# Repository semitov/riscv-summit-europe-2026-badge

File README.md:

# RISC-V Summit Europe 2026 Badge

Electronic badge PCB for RISC-V Summit Europe 2026 in Bologna, Italy. Designed in KiCad 10.

## Gallery

- Render of the badge on KiCad

## License and Credits
Designed by: [Tan Siret Akıncı](https://github.com/tansiret), [Emanuele De Paoli](https://github.com/Irdyad), [Carlo Bendelli](https://github.com/CALIOSTRO7), [Valerio Donnini](https://github.com/Valerio-Donnini) and [Alessandro Bocchino](https://github.com/AleB-04).
This open source hardware project is licensed with [CERN-OHL-W](LICENSE). The project is sponsored by © 2026 [RISC-V International](), [NextPCB](https://www.nextpcb.com/), [GOWIN Semiconductor](https://www.gowinsemi.com/en/) and  [DeepComputing](https://deepcomputing.io/).
The project has been certified by [OSHWA](https://oshwa.org/) as Open Source Hardware (UID: [IT000028](https://certification.oshwa.org/it000028.html)).
</br>

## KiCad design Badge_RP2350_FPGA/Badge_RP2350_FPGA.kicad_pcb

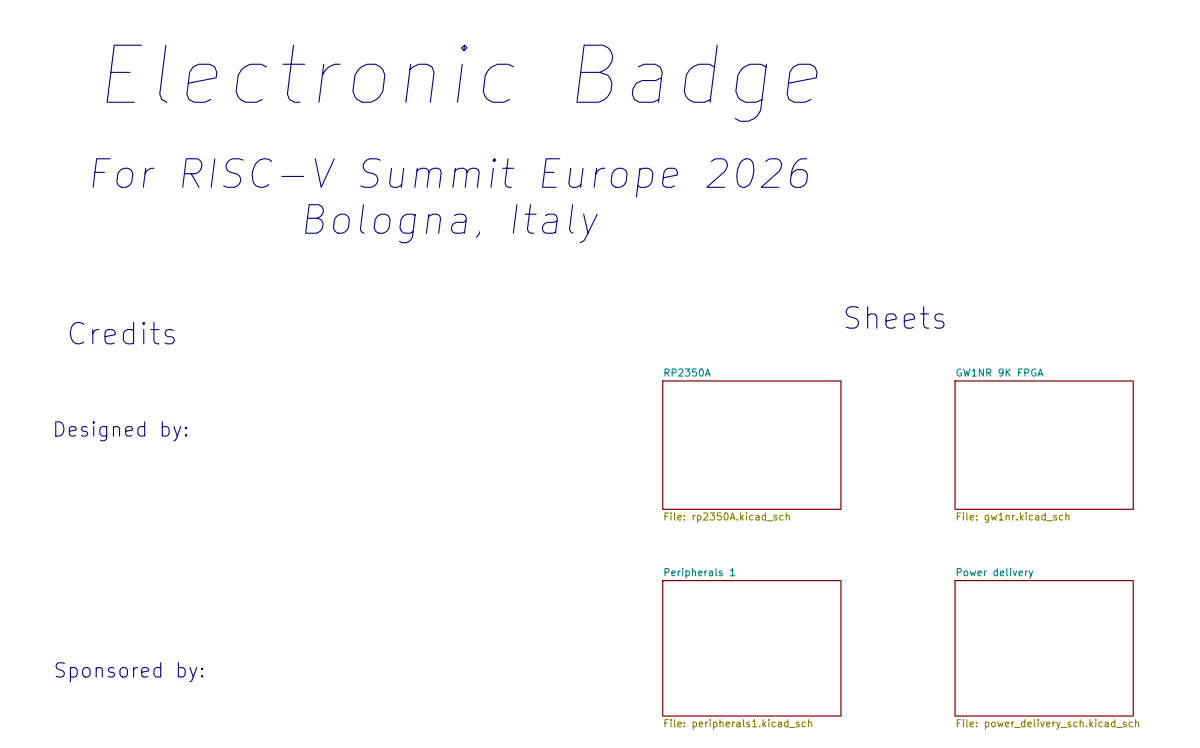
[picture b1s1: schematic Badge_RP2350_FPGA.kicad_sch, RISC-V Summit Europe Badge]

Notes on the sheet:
Sheets
Credits
Electronic Badge
Sponsored by:
For RISC-V Summit Europe 2026 Bologna, Italy
Designed by:

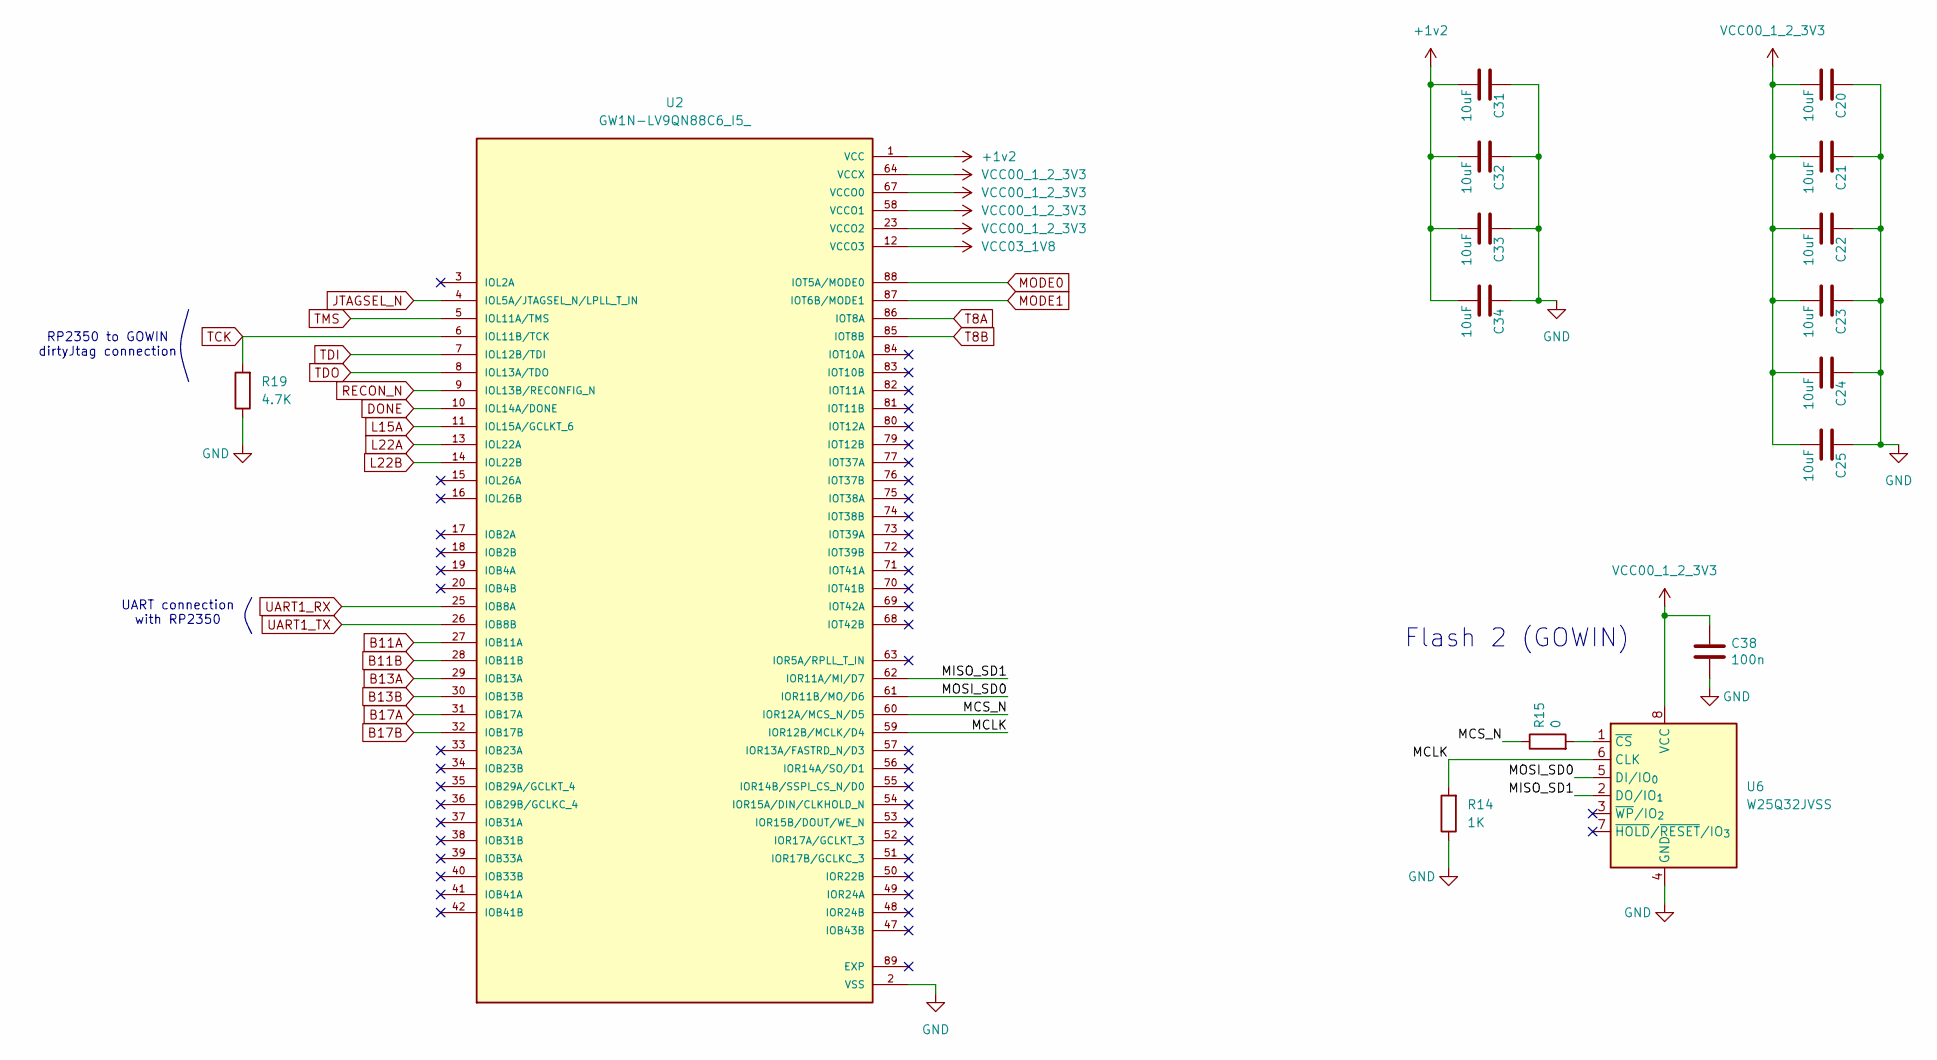
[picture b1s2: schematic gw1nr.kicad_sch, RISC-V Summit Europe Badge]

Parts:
C20, C21, C22, C23, C24, C25, C31, C32, C33, C34: 10uF; C_0402_1005Metric
C38: 100n; C_0402_1005Metric
R14: 1K; R_0402_1005Metric
R15: 0; R_0402_1005Metric
R19: 4.7K; R_0402_1005Metric
U2: GW1N-LV9QN88C6_I5_; QFN40P1000X1000X95-89N; PARTREV UG103-2.3E
U6: W25Q32JVSS; SOIC-8_5.3x5.3mm_P1.27mm

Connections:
/GW1NR 9K FPGA/MCLK: R14.2, U2.59 (IOR12B/MCLK/D4), U6.6 (CLK)
/GW1NR 9K FPGA/MCS_N: R15.1, U2.60 (IOR12A/MCS_N/D5)
/GW1NR 9K FPGA/MISO_SD1: U2.62 (IOR11A/MI/D7), U6.2 (DO/IO_{1})
/GW1NR 9K FPGA/MOSI_SD0: U2.61 (IOR11B/MO/D6), U6.5 (DI/IO_{0})
B11A: U2.27 (IOB11A); also elsewhere on the board
B11B: U2.28 (IOB11B); also elsewhere on the board
B13A: U2.29 (IOB13A); also elsewhere on the board
B13B: U2.30 (IOB13B); also elsewhere on the board
B17A: U2.31 (IOB17A); also elsewhere on the board
B17B: U2.32 (IOB17B); also elsewhere on the board
DONE: U2.10 (IOL14A/DONE); also elsewhere on the board
GND: C20.1, C21.1, C22.1, C23.1, C24.1, C25.1, C31.1, C32.1, C33.1, C34.1, C38.2, R14.1, R19.1, U2.2 (VSS), U2.21 (VSS), U2.24 (VSS), U2.43 (VSS), U2.46 (VSS), U2.65 (VSS), U6.4 (GND); also elsewhere on the board
JTAGSEL_N: U2.4 (IOL5A/JTAGSEL_N/LPLL_T_IN); also elsewhere on the board
L15A: U2.11 (IOL15A/GCLKT_6); also elsewhere on the board
L22A: U2.13 (IOL22A); also elsewhere on the board
L22B: U2.14 (IOL22B); also elsewhere on the board
MODE0: U2.88 (IOT5A/MODE0); also elsewhere on the board
MODE1: U2.87 (IOT6B/MODE1); also elsewhere on the board
unnamed: R15.2, U6.1 (~CS)
RECON_N: U2.9 (IOL13B/RECONFIG_N); also elsewhere on the board
T8A: U2.86 (IOT8A); also elsewhere on the board
T8B: U2.85 (IOT8B); also elsewhere on the board
TCK: R19.2, U2.6 (IOL11B/TCK); also elsewhere on the board
TDI: U2.7 (IOL12B/TDI); also elsewhere on the board
TDO: U2.8 (IOL13A/TDO); also elsewhere on the board
TMS: U2.5 (IOL11A/TMS); also elsewhere on the board
UART1_RX: U2.25 (IOB8A); also elsewhere on the board
UART1_TX: U2.26 (IOB8B); also elsewhere on the board
VCC00_1_2_3V3: C20.2, C21.2, C22.2, C23.2, C24.2, C25.2, C38.1, U2.23 (VCCO2), U2.44 (VCCO2), U2.58 (VCCO1), U2.64 (VCCX), U2.67 (VCCO0), U2.78 (VCCX), U6.8 (VCC); also elsewhere on the board
VCC03_1V8: U2.12 (VCCO3); also elsewhere on the board

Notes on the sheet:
RP2350 to GOWIN dirtyJtag connection
UART connection with RP2350
Flash 2 (GOWIN)

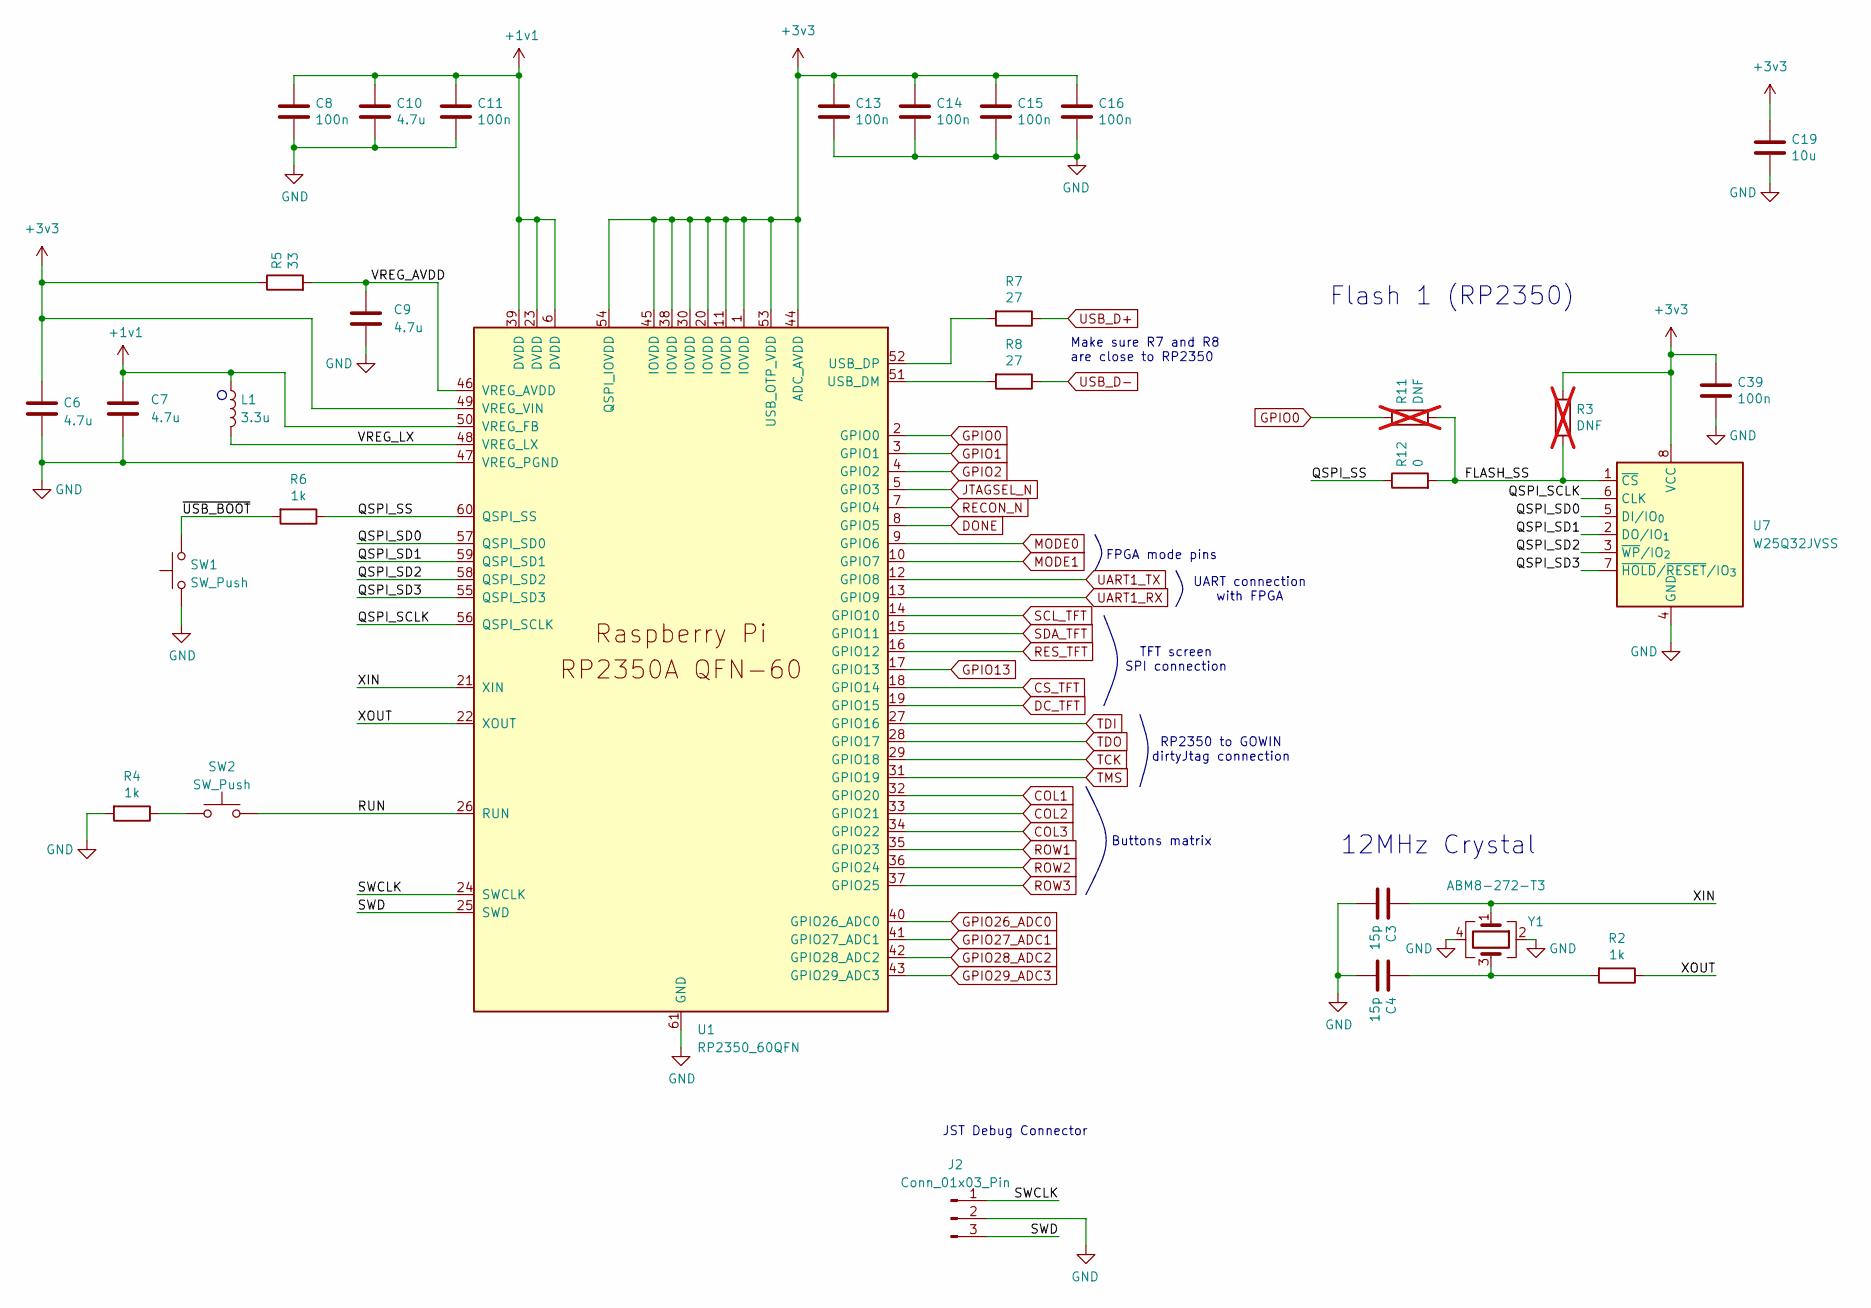
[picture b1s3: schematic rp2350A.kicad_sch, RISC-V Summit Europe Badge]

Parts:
C3, C4: 15p; C_0402_1005Metric
C6, C7, C9, C10: 4.7u; C_0402_1005Metric
C8, C11, C13, C14, C15, C16, C39: 100n; C_0402_1005Metric
C19: 10u; C_0805_2012Metric
J2: Conn_01x03_Pin; PinHeader_1x03_P2.54mm_Vertical
L1: 3.3u; L_pol_2016
R2, R4, R6: 1k; R_0402_1005Metric
R3, R11: DNF; R_0402_1005Metric; not fitted
R5: 33; R_0402_1005Metric
R7, R8: 27; R_0402_1005Metric
R12: 0; R_0402_1005Metric
SW1, SW2: SW_Push; C&K KMR621NGLFS
U1: RP2350_60QFN; RP2350-QFN-60-1EP_7x7_P0.4mm_EP3.4x3.4mm_ThermalVias
U7: W25Q32JVSS; SOIC-8_5.3x5.3mm_P1.27mm
Y1: ABM8-272-T3; Crystal_SMD_3225-4Pin_3.2x2.5mm

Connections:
+1v1: C7.1, C8.1, C10.1, C11.1, L1.1, U1.6 (DVDD), U1.23 (DVDD), U1.39 (DVDD), U1.50 (VREG_FB)
+3v3: C6.1, C13.1, C14.1, C15.1, C16.1, C19.1, C39.1, R3.1, R5.1, U1.1 (IOVDD), U1.11 (IOVDD), U1.20 (IOVDD), U1.30 (IOVDD), U1.38 (IOVDD), U1.44 (ADC_AVDD), U1.45 (IOVDD), U1.49 (VREG_VIN), U1.53 (USB_OTP_VDD), U1.54 (QSPI_IOVDD), U7.8 (VCC); also elsewhere on the board
/RP2350A/FLASH_SS: R3.2, R11.2, R12.2, U7.1 (~CS)
/RP2350A/QSPI_SCLK: U1.56 (QSPI_SCLK), U7.6 (CLK)
/RP2350A/QSPI_SD0: U1.57 (QSPI_SD0), U7.5 (DI/IO_{0})
/RP2350A/QSPI_SD1: U1.59 (QSPI_SD1), U7.2 (DO/IO_{1})
/RP2350A/QSPI_SD2: U1.58 (QSPI_SD2), U7.3 (~WP/IO_{2})
/RP2350A/QSPI_SD3: U1.55 (QSPI_SD3), U7.7 (~HOLD/~RESET/IO_{3})
/RP2350A/QSPI_SS: R6.1, R12.1, U1.60 (QSPI_SS)
/RP2350A/RUN: SW2.2, U1.26 (RUN)
/RP2350A/SWCLK: J2.1, U1.24 (SWCLK)
/RP2350A/SWD: J2.3, U1.25 (SWD)
/RP2350A/VREG_AVDD: C9.1, R5.2, U1.46 (VREG_AVDD)
/RP2350A/VREG_LX: L1.2, U1.48 (VREG_LX)
/RP2350A/XIN: C3.1, U1.21 (XIN), Y1.1
/RP2350A/XOUT: R2.1, U1.22 (XOUT)
/RP2350A/~USB_BOOT: R6.2, SW1.2
COL1: U1.32 (GPIO20); also elsewhere on the board
COL2: U1.33 (GPIO21); also elsewhere on the board
COL3: U1.34 (GPIO22); also elsewhere on the board
CS_TFT: U1.18 (GPIO14); also elsewhere on the board
DC_TFT: U1.19 (GPIO15); also elsewhere on the board
DONE: U1.8 (GPIO5); also elsewhere on the board
GND: C3.2, C4.2, C6.2, C7.2, C8.2, C9.2, C10.2, C11.2, C13.2, C14.2, C15.2, C16.2, C19.2, C39.2, J2.2, R4.2, SW1.1, U1.47 (VREG_PGND), U1.61 (GND), U7.4 (GND), Y1.2, Y1.4; also elsewhere on the board
GPIO0: R11.1, U1.2 (GPIO0); also elsewhere on the board
GPIO1: U1.3 (GPIO1)
GPIO2: U1.4 (GPIO2)
GPIO13: U1.17 (GPIO13)
GPIO26_ADC0: U1.40 (GPIO26_ADC0); also elsewhere on the board
GPIO27_ADC1: U1.41 (GPIO27_ADC1); also elsewhere on the board
GPIO28_ADC2: U1.42 (GPIO28_ADC2); also elsewhere on the board
GPIO29_ADC3: U1.43 (GPIO29_ADC3); also elsewhere on the board
JTAGSEL_N: U1.5 (GPIO3); also elsewhere on the board
MODE0: U1.9 (GPIO6); also elsewhere on the board
MODE1: U1.10 (GPIO7); also elsewhere on the board
unnamed: C4.1, R2.2, Y1.3
unnamed: R4.1, SW2.1
unnamed: R8.2, U1.51 (USB_DM)
unnamed: R7.2, U1.52 (USB_DP)
RECON_N: U1.7 (GPIO4); also elsewhere on the board
RES_TFT: U1.16 (GPIO12); also elsewhere on the board
ROW1: U1.35 (GPIO23); also elsewhere on the board
ROW2: U1.36 (GPIO24); also elsewhere on the board
ROW3: U1.37 (GPIO25); also elsewhere on the board
SCL_TFT: U1.14 (GPIO10); also elsewhere on the board
SDA_TFT: U1.15 (GPIO11); also elsewhere on the board
TCK: U1.29 (GPIO18); also elsewhere on the board
TDI: U1.27 (GPIO16); also elsewhere on the board
TDO: U1.28 (GPIO17); also elsewhere on the board
TMS: U1.31 (GPIO19); also elsewhere on the board
UART1_RX: U1.13 (GPIO9); also elsewhere on the board
UART1_TX: U1.12 (GPIO8); also elsewhere on the board
USB_D+: R7.1; also elsewhere on the board
USB_D-: R8.1; also elsewhere on the board

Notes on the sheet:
Flash 1 (RP2350)
JST Debug Connector
Make sure R7 and R8 are close to RP2350
TFT screen SPI connection
FPGA mode pins
UART connection with FPGA
Buttons matrix
RP2350 to GOWIN dirtyJtag connection
12MHz Crystal

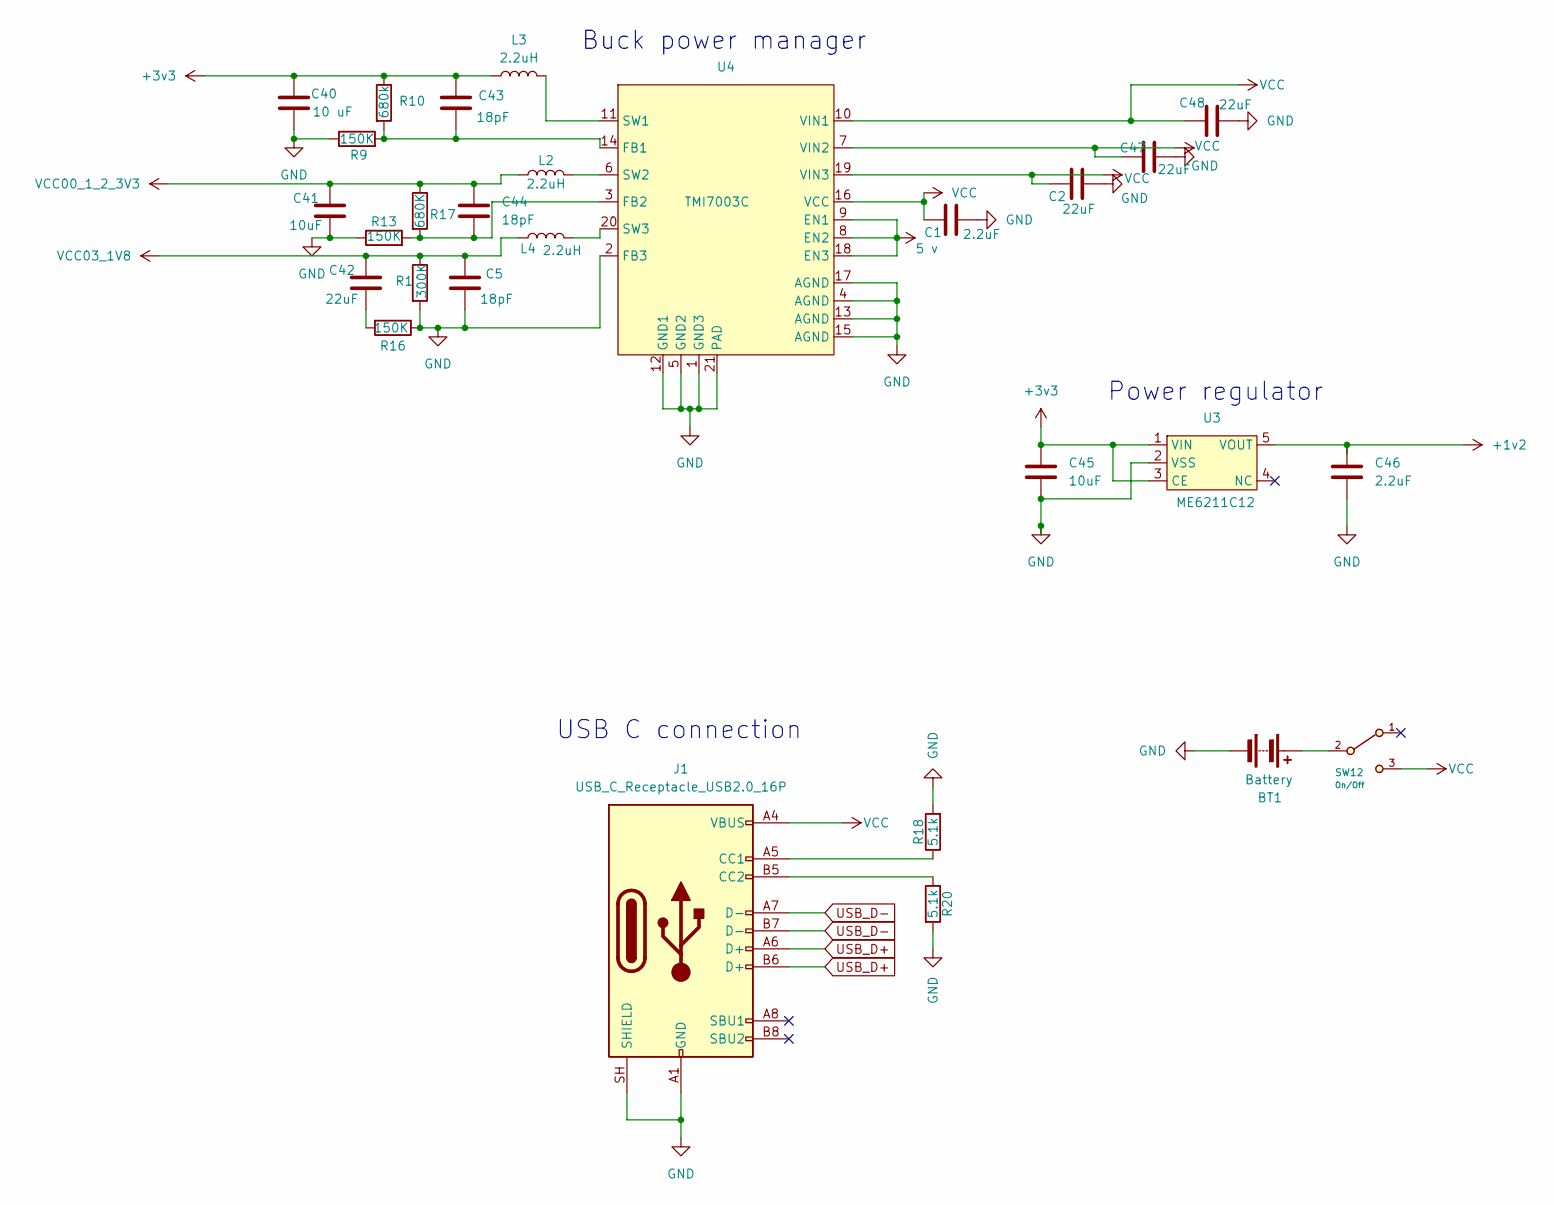
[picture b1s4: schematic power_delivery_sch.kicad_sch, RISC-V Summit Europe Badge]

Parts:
BT1: Battery; BatteryHolder_Keystone_2462_2xAA
C1, C46: 2.2uF; C_0402_1005Metric
C2, C42, C47, C48: 22uF; C_0402_1005Metric
C5, C43, C44: 18pF; C_0402_1005Metric
C40: 10 uF; C_0402_1005Metric
C41, C45: 10uF; C_0402_1005Metric
J1: USB_C_Receptacle_USB2.0_16P; USB_C_Receptacle_HRO_TYPE-C-31-M-12
L2, L3, L4: 2.2uH; L_APV_ANR4018
R1: 300K; R_0402_1005Metric
R9, R13, R16: 150K; R_0402_1005Metric
R10: 680k; R_0402_1005Metric
R17: 680K; R_0402_1005Metric
R18, R20: 5.1k; R_0402_1005Metric
SW12: On/Off; C&K JS102011SAQN
U3: ME6211C12; SOT-23-5_L3.0-W1.7-P0.95-LS2.8-BL
U4: TMI7003C; QFN-20_L3.0-W3.0-P0.40-BL-EP1.7

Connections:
5 v: U4.8 (EN2), U4.9 (EN1), U4.18 (EN3)
+3v3: C40.1, C43.1, C45.1, L3.1, R10.1, U3.1 (VIN), U3.3 (CE); also elsewhere on the board
GND: BT1.2 (-), C1.2, C2.2, C5.2, C40.2, C41.2, C45.2, C46.2, C47.2, C48.2, J1.A1 (GND), J1.A12 (GND), J1.B1 (GND), J1.B12 (GND), J1.SH (SHIELD), R1.2, R9.1, R13.1, R16.1, R18.2, R20.2, U3.2 (VSS), U4.1 (GND3), U4.2 (FB3), U4.4 (AGND), U4.5 (GND2), U4.12 (GND1), U4.13 (AGND), U4.15 (AGND), U4.17 (AGND), U4.21 (PAD); also elsewhere on the board
unnamed: BT1.1 (+), SW12.2 (B)
unnamed: C42.2, R16.2
unnamed: J1.A5 (CC1), R18.1
unnamed: J1.B5 (CC2), R20.1
unnamed: C43.2, R9.2, R10.2, U4.14 (FB1)
unnamed: C44.2, R13.2, R17.2, U4.3 (FB2)
unnamed: L3.2, U4.11 (SW1)
unnamed: L2.2, U4.6 (SW2)
unnamed: L4.2, U4.20 (SW3)
USB_D+: J1.A6 (D+), J1.B6 (D+); also elsewhere on the board
USB_D-: J1.A7 (D-), J1.B7 (D-); also elsewhere on the board
VCC00_1_2_3V3: C41.1, C44.1, L2.1, R17.1; also elsewhere on the board
VCC03_1V8: C5.1, C42.1, L4.1, R1.1; also elsewhere on the board

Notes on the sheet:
Power regulator
USB C connection
Buck power manager

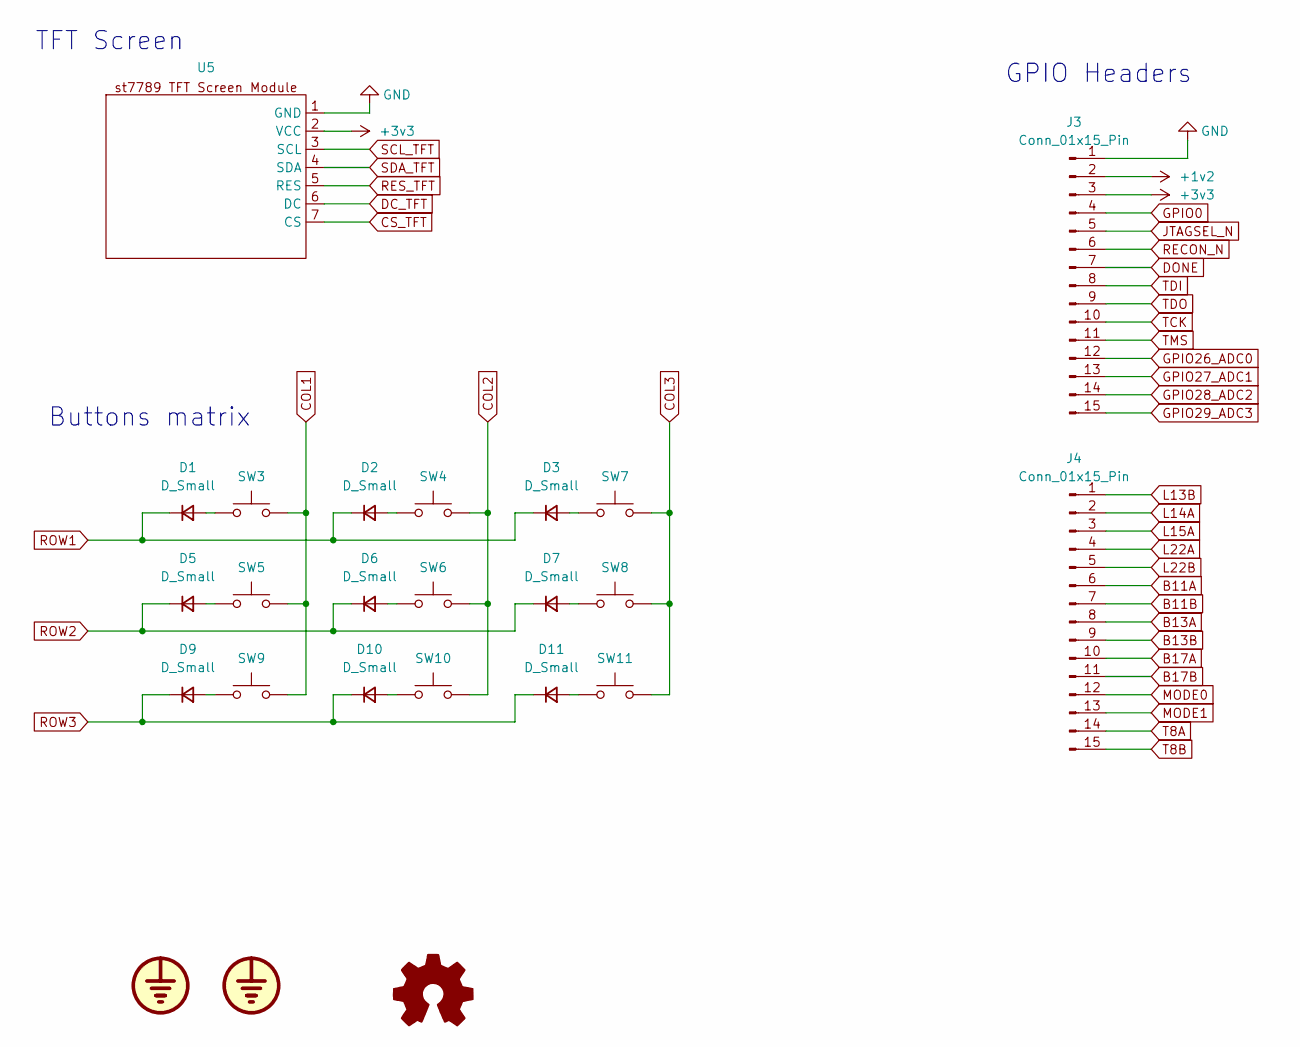
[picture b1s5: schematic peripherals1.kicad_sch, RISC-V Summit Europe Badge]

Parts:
D1, D2, D3, D5, D6, D7, D9, D10, D11: D_Small; Nexperia BAS516,115
J3, J4: Conn_01x15_Pin; PinHeader_1x15_P2.54mm_Vertical
SW3, SW4, SW5, SW6, SW7, SW8, SW9, SW10, SW11: SHOU HAN TS665PA 250gf
U5: st7789_7pin_noblk

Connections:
+3v3: J3.3, U5.2 (VCC); also elsewhere on the board
B11A: J4.6; also elsewhere on the board
B11B: J4.7; also elsewhere on the board
B13A: J4.8; also elsewhere on the board
B13B: J4.9; also elsewhere on the board
B17A: J4.10; also elsewhere on the board
B17B: J4.11; also elsewhere on the board
COL1: SW3.2, SW5.2, SW9.2; also elsewhere on the board
COL2: SW4.2, SW6.2, SW10.2; also elsewhere on the board
COL3: SW7.2, SW8.2, SW11.2; also elsewhere on the board
CS_TFT: U5.7 (CS); also elsewhere on the board
DC_TFT: U5.6 (DC); also elsewhere on the board
DONE: J3.7; also elsewhere on the board
GND: J3.1, U5.1 (GND); also elsewhere on the board
GPIO0: J3.4; also elsewhere on the board
GPIO26_ADC0: J3.12; also elsewhere on the board
GPIO27_ADC1: J3.13; also elsewhere on the board
GPIO28_ADC2: J3.14; also elsewhere on the board
GPIO29_ADC3: J3.15; also elsewhere on the board
JTAGSEL_N: J3.5; also elsewhere on the board
L13B: J4.1
L14A: J4.2
L15A: J4.3; also elsewhere on the board
L22A: J4.4; also elsewhere on the board
L22B: J4.5; also elsewhere on the board
MODE0: J4.12; also elsewhere on the board
MODE1: J4.13; also elsewhere on the board
unnamed: D1.2 (A), SW3.1
unnamed: D2.2 (A), SW4.1
unnamed: D3.2 (A), SW7.1
unnamed: D5.2 (A), SW5.1
unnamed: D6.2 (A), SW6.1
unnamed: D7.2 (A), SW8.1
unnamed: D9.2 (A), SW9.1
unnamed: D10.2 (A), SW10.1
unnamed: D11.2 (A), SW11.1
RECON_N: J3.6; also elsewhere on the board
RES_TFT: U5.5 (RES); also elsewhere on the board
ROW1: D1.1 (K), D2.1 (K), D3.1 (K); also elsewhere on the board
ROW2: D5.1 (K), D6.1 (K), D7.1 (K); also elsewhere on the board
ROW3: D9.1 (K), D10.1 (K), D11.1 (K); also elsewhere on the board
SCL_TFT: U5.3 (SCL); also elsewhere on the board
SDA_TFT: U5.4 (SDA); also elsewhere on the board
T8A: J4.14; also elsewhere on the board
T8B: J4.15; also elsewhere on the board
TCK: J3.10; also elsewhere on the board
TDI: J3.8; also elsewhere on the board
TDO: J3.9; also elsewhere on the board
TMS: J3.11; also elsewhere on the board

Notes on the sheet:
Buttons matrix
TFT Screen
GPIO Headers

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
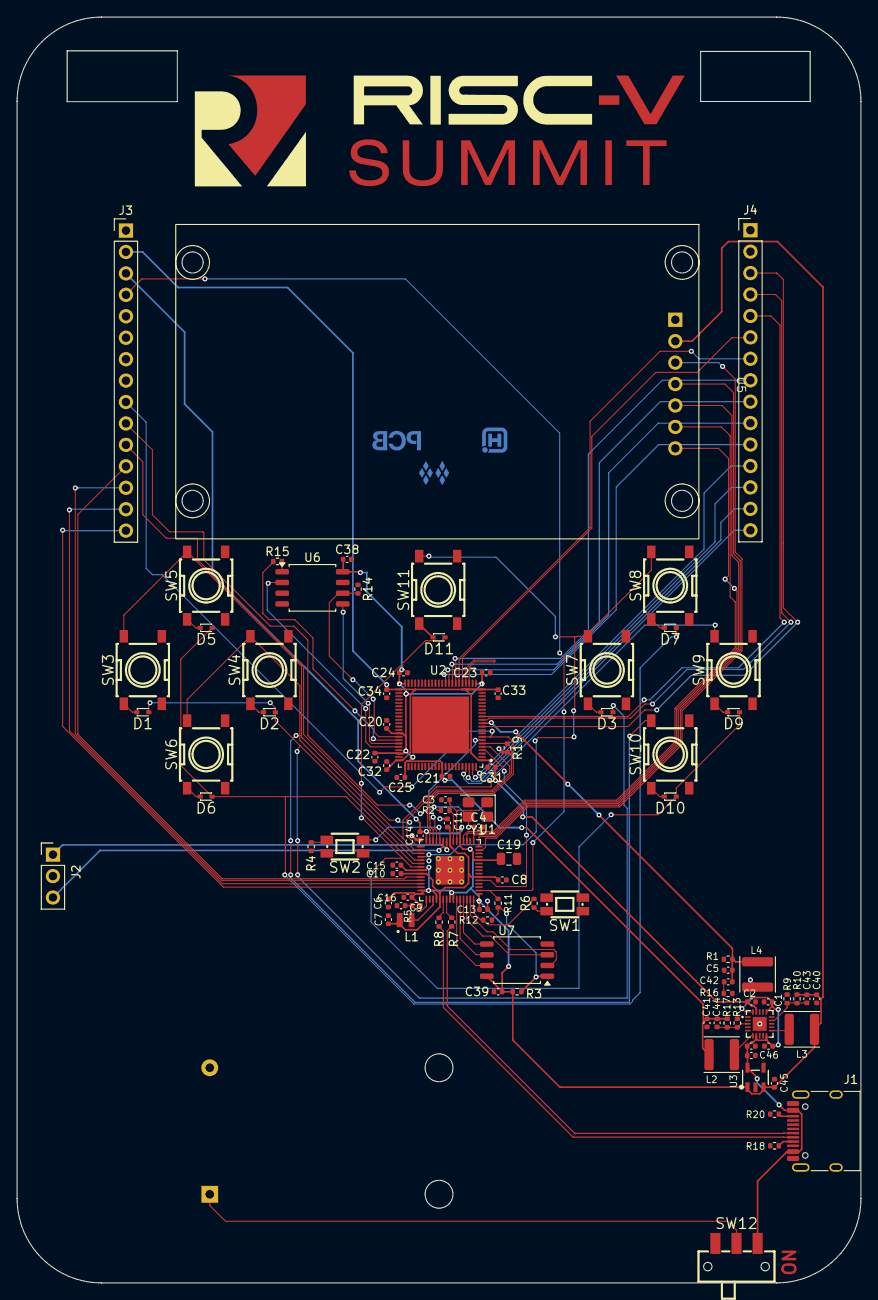
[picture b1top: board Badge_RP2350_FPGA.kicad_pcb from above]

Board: 2 copper layers, 100.0 x 150.0 mm, 95 parts (1 on the bottom side), 89 nets.

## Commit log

2026-03-30 initial commit - very basic work done so far
2026-04-08 add new schematic and footprint element (subject for verification, and edit schematics a bit
2026-04-09 add jtag connection
2026-04-09 edit custom st7789 footprint
2026-04-14 add buttons by Arianna and make Flash 2 shared between 2 chips
2026-04-14 Revert "First commit" by Alessandro pushed to main
    This reverts commit f61961a8b610eca0a4065d845ac8c1bd7211c9eb.
2026-04-23 added the folders for each division
2026-04-23 added the readme files
2026-04-24 Added Datapath subproject
2026-05-02 add power delivery by Carlo
2026-05-02 edit readme and add CERH OHL-W license
2026-05-04 add type c port and uart connections
2026-05-04 modify usb and flash connections
2026-05-05 edit schematics, add global pins
2026-05-06 assign all footprints and import to pcb
2026-05-06 started PCB layout
2026-05-06 add headers and fix voltage references
2026-05-06 add x to unused pins and connect more pins
2026-05-06 almost finished component placement
2026-05-08 add jtagsel_n connection
2026-05-08 add more FPGA connections and generate netlist, bom
2026-05-11 update footprints, connections, some labels and more
2026-05-13 add PCB silkscreen-copper art
2026-05-14 edit schematics visually and edit pcb
2026-05-14 fix missing library
2026-05-14 edit pcb placement slightly
2026-05-14 power placement
2026-05-15 M: pcb routing start, minor schematic changes
2026-05-18 Routing progress
2026-05-18 Update PCB routing
2026-05-19 U: PCB routing
2026-05-19 finalize the design, add photos
2026-05-20 M: better GND coverage, fixed floating net
2026-05-20 add art, stuff
2026-05-20 redefine clearance, edit routing
2026-05-20 add art by Alisa Chen
2026-05-20 add one more sponsor and bigger repo qr code
2026-05-20 fix name in credits
2026-05-20 generate gerbers
2026-05-20 F: DRC and USB-C
2026-05-20 edit pcb and generate gerber files, centroid file
2026-05-20 refactor(readme): remove duplicated gallery header
2026-05-20 add OSHWA UID IT000028
2026-05-20 typo
2026-05-21 edit silkscreen etc
2026-05-21 fixes

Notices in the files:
Badge_RP2350_FPGA/Badge_RP2350_FPGA.kicad_pcb:
License: CERN-OHL-W-2.0
CERN-OHL-W 2.0
